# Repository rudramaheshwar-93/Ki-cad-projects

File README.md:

# 🧩 KiCad PCB Projects

A curated collection of PCB designs created using **KiCad**, focused on digital and analog circuit implementations for learning and practical applications.

---

## 📁 Projects

### 🔔 Buzzer PCB

* Simple buzzer driver circuit
* Designed for controlled switching
* 2-layer PCB
  👉 *Includes schematic, PCB layout, and Gerber files*

---

### 🔌 Voltage Regulator PCB (5V → 3.3V)

* LDO-based voltage regulation
* Suitable for ESP32, STM32, and IoT applications
* Stable and compact design
* 2-layer PCB
  👉 *Optimized for clean power delivery*

---

### ➕ Full Adder PCB

* Digital logic implementation of a full adder
* Uses XOR, AND, OR gates
* Demonstrates combinational logic design
* 2-layer PCB
  👉 *Ideal for understanding basic digital circuits*

---

## 🛠️ Tools Used

* KiCad 7.0

---

## 📦 Features

* Clean and readable schematics
* Well-routed PCB layouts
* Manufacturing-ready Gerber files
* Beginner-friendly designs

---

## 🏭 Manufacturing

All projects include **Gerber files** that can be directly uploaded to:

* JLCPCB
* PCBWay

---

## 👤 Author

**Chappidi Rudra Maheshwar Reddy**

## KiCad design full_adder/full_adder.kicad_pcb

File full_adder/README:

# ➕ Full Adder PCB Design

## 📌 Overview

This project implements a **Full Adder circuit** using discrete digital logic gates on a custom-designed PCB.

A full adder performs binary addition of three inputs:

* A
* B
* Carry-in (Cin)

It produces:

* Sum
* Carry-out (Cout)

---

## ⚡ Key Specifications

* Logic Gates Used: XOR, AND, OR
* Function: Binary addition (combinational logic)
* Layers: 2-layer PCB
* Designed using: KiCad

---

## 🔧 Working Principle

* **Sum = A ⊕ B ⊕ Cin**
* **Carry = (A·B) + (Cin·(A ⊕ B))**

This design demonstrates fundamental digital logic implementation on hardware.

---

## 📂 Files Included

* `full_adder.kicad_sch` — Schematic file
* `full_adder.kicad_pcb` — PCB layout file
* `/gerber` — Manufacturing-ready files

---

## 🛠️ Tools Used

* KiCad 7.0

---

## 🏭 Manufacturing

The Gerber files are ready for fabrication using:

* JLCPCB
* PCBWay

---

## 📚 Learning Outcomes

* Understanding combinational logic circuits
* PCB design workflow using KiCad
* Practical implementation of digital electronics

---

## 👤 Author

**Chappidi Rudra Maheshwar Reddy**

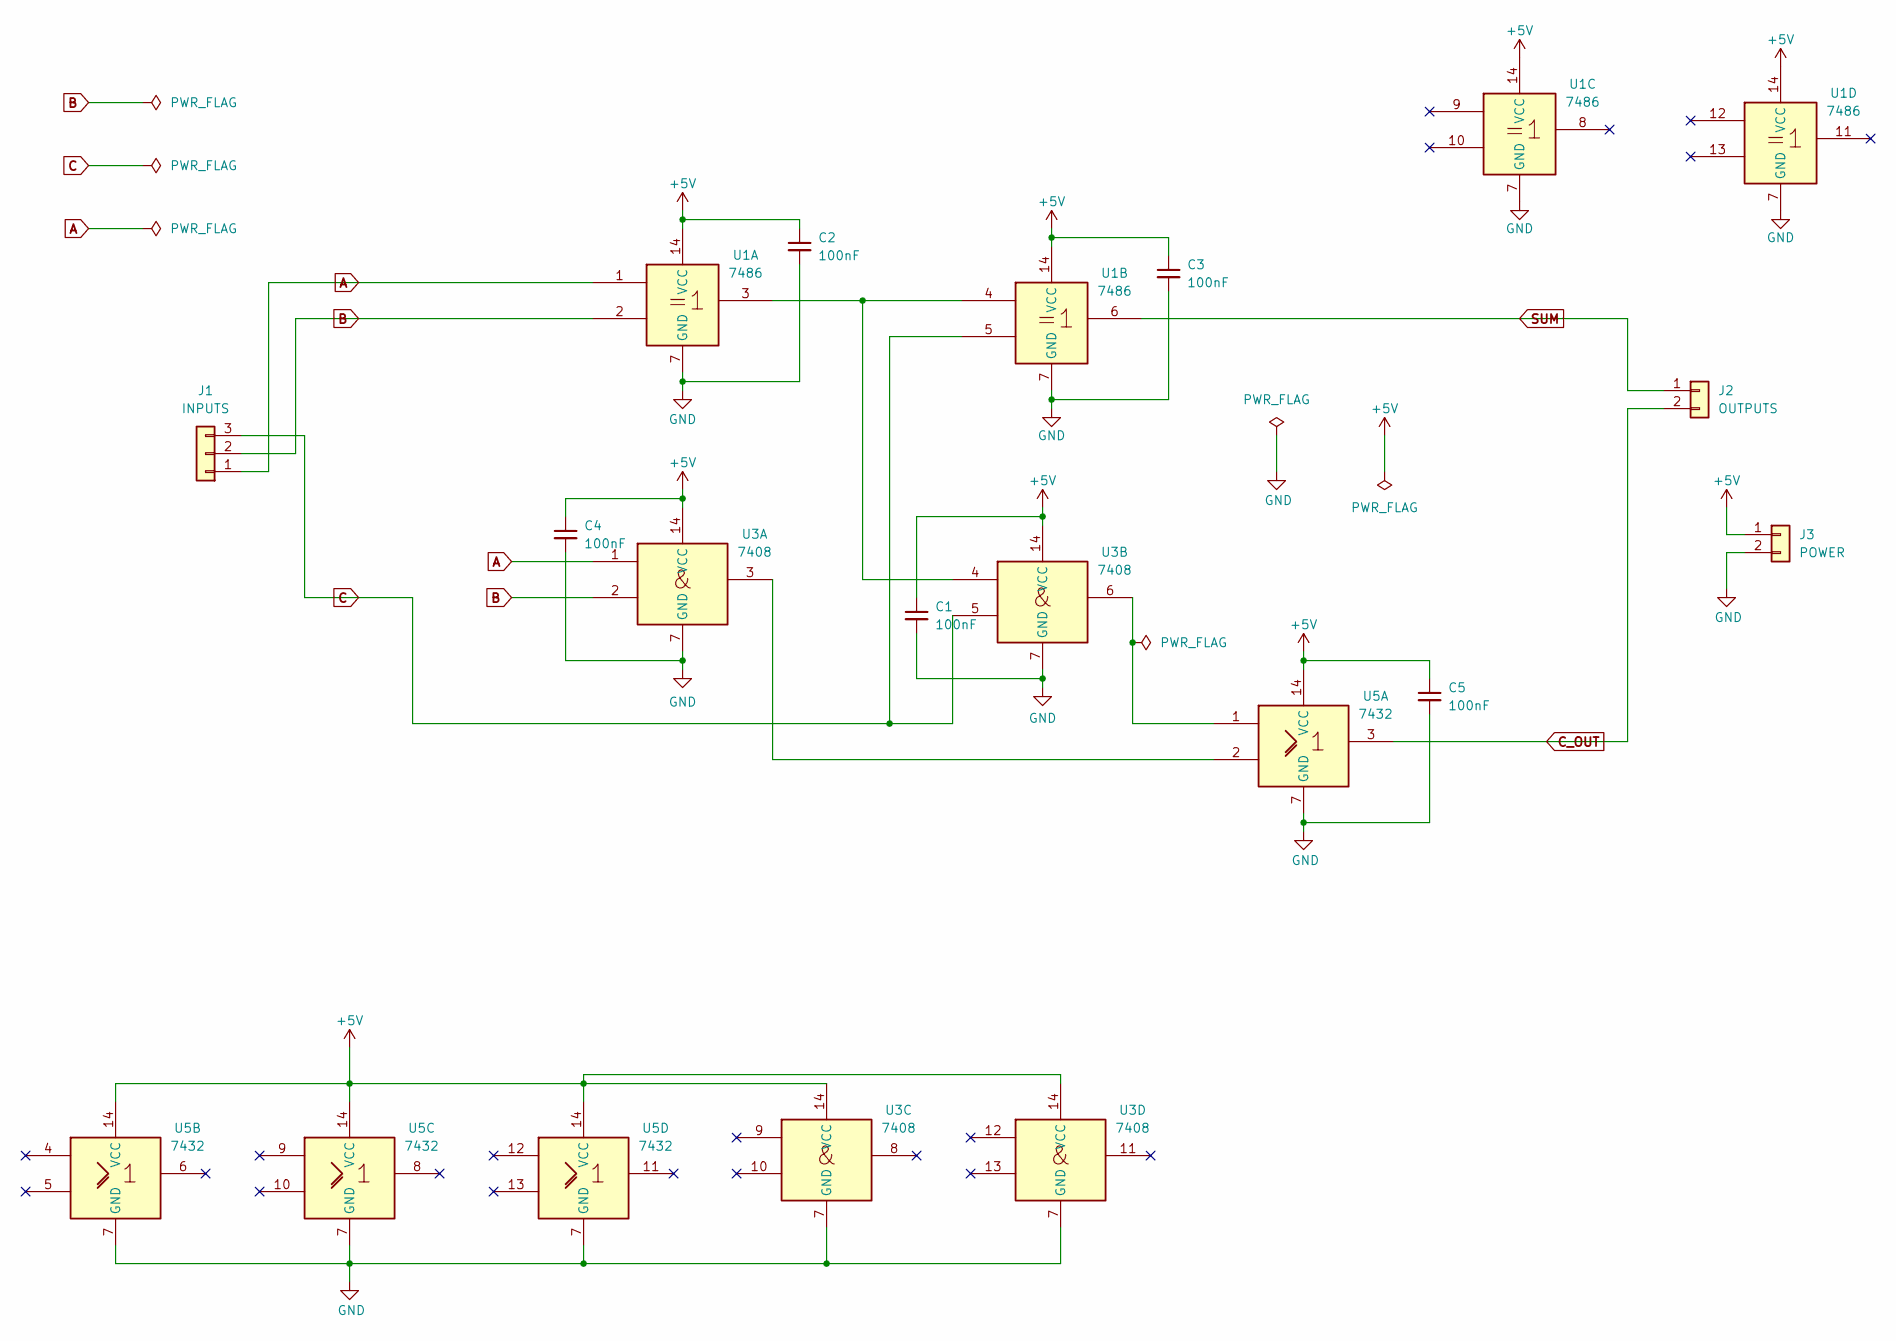
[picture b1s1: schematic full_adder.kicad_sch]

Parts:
C1, C2, C3, C4, C5: 100nF; C_Disc_D5.0mm_W2.5mm_P2.50mm
J1: INPUTS; PinHeader_1x03_P2.54mm_Vertical
J2: OUTPUTS; PinHeader_1x02_P2.54mm_Vertical
J3: POWER; PinHeader_1x02_P2.54mm_Vertical
U1: 7486; DIP-14_W7.62mm
U3: 7408; DIP-14_W7.62mm
U5: 7432; DIP-14_W7.62mm

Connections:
+5V: C1.1, C2.1, C3.1, C4.1, C5.1, J3.1, U1.14 (VCC), U3.14 (VCC), U5.14 (VCC)
A: J1.1, U1.1, U3.1
B: J1.2, U1.2, U3.2
C: J1.3, U1.5, U3.5
C_OUT: J2.2, U5.3
GND: C1.2, C2.2, C3.2, C4.2, C5.2, J3.2, U1.7 (GND), U3.7 (GND), U5.7 (GND)
unnamed: U1.3, U1.4, U3.4
unnamed: U3.3, U5.2
unnamed: U3.6, U5.1
SUM: J2.1, U1.6

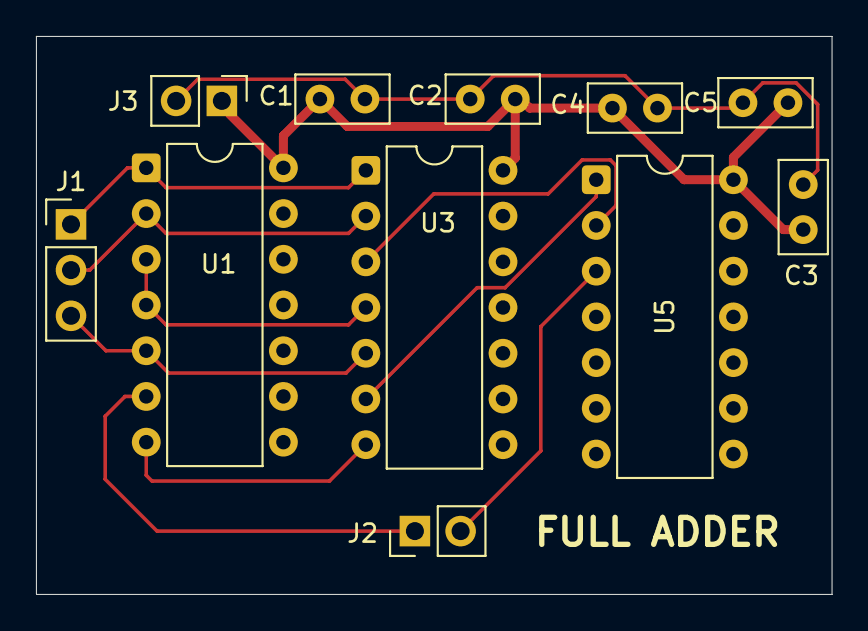
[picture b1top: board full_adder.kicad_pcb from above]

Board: 2 copper layers, 44.2 x 31.0 mm, 11 parts (0 on the bottom side), 10 nets.

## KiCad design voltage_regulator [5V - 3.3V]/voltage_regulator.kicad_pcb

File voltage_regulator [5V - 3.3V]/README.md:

# Voltage Regulator PCB (5V to 3.3V)

## 📌 Overview
A compact 2-layer PCB designed to regulate a 5V input supply down to a
stable 3.3V output using an LDO (Low Dropout) voltage regulator.
Designed for use in embedded systems and IoT applications where 3.3V
logic level components like ESP32, STM32, and nRF24L01 require a clean,
stable power supply.

## ⚡ Key Specifications
- Input Voltage: 5V (USB or external supply)
- Output Voltage: 3.3V regulated
- Regulator Type: LDO (Low Dropout)
- Maximum Output Current: 800mA
- Layers: 2-layer PCB
- PCB Size: compact form factor
- Designed using: KiCad 7.0

## 🖼️ PCB Preview
<!-- Add your 3D render screenshot here -->

## 📂 Repository Structure
​```
voltage-regulator-pcb/
├── voltage_regulator.kicad_pcb   → PCB layout file
├── voltage_regulator.kicad_sch   → Schematic file
├── voltage_regulator.kicad_pro   → Project file
├── gerber/                       → Manufacturing files
│   ├── voltage_regulator-F_Cu.gbr
│   ├── voltage_regulator-B_Cu.gbr
│   ├── voltage_regulator-Edge_Cuts.gbr
│   └── voltage_regulator-job.gbrjob
└── README.md
​```

## 🔧 Components Used
| Component | Value | Purpose |
|---|---|---|
| U1 | AMS1117-3.3 / LM1117 | LDO Voltage Regulator |
| C1 | 10µF Electrolytic | Input Decoupling Capacitor |
| C2 | 10µF Electrolytic | Output Decoupling Capacitor |
| C3 | 100nF Ceramic | High Frequency Bypass |
| LED1 | Green LED | Power Indicator |
| R1 | 1kΩ | LED Current Limiting Resistor |
| J1 | 2-pin Connector | Input (5V) |
| J2 | 2-pin Connector | Output (3.3V) |

## 🔌 How It Works
1. 5V input is fed through J1 connector
2. Input decoupling capacitor C1 filters supply noise
3. LDO regulator drops voltage from 5V to stable 3.3V
4. Output capacitor C2 ensures stability and reduces ripple
5. Green LED indicates the board is powered and outputting correctly
6. Clean 3.3V output is available at J2 connector

## 📐 Design Decisions
- Used AMS1117-3.3 LDO for its wide availability and low dropout voltage
- Added both electrolytic and ceramic capacitors for broadband noise filtering
- Power indicator LED helps verify output during testing without a multimeter
- Wide power traces (0.5mm+) to handle up to 800mA current safely

## 🏭 Manufacturing
Gerber files in `/gerber` folder are tested and verified with zero
DRC errors. Ready to order directly from:
- JLCPCB — jlcpcb.com
- PCBWay — pcbway.com

## 🛠️ Tools Used
- KiCad 7.0 — PCB design and schematic capture
- LTspice — Pre-layout voltage regulation simulation

## 👤 Author
Chappidi Rudra Maheshwar Reddy
GitHub: github.com/rudramaheshwar-93

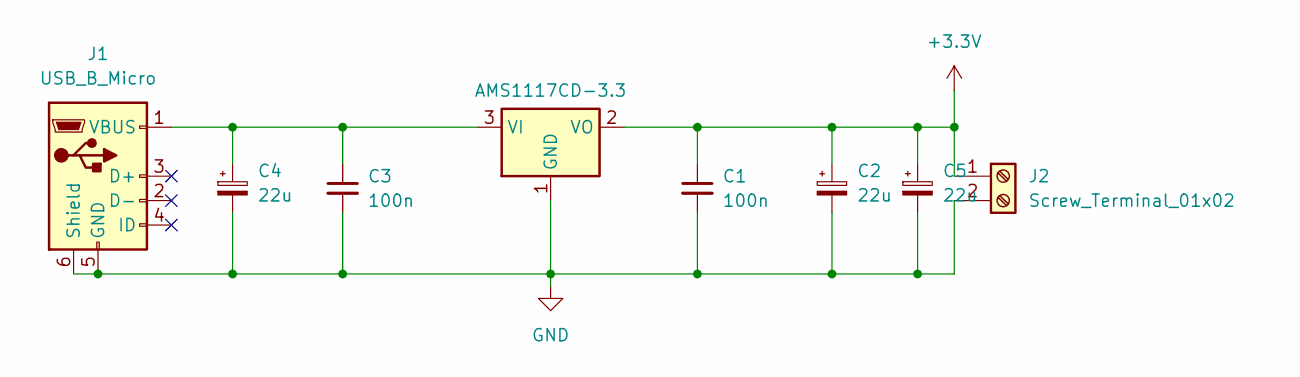
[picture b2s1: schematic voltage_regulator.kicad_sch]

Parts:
C1, C3: 100n; C_01005_0402Metric
C2, C4, C5: 22u; CP_Elec_6.3x7.7
J1: USB_B_Micro; USB_Micro-B_Molex_47346-0001
J2: Screw_Terminal_01x02; TerminalBlock_Phoenix_MKDS-3-2-5.08_1x02_P5.08mm_Horizontal
U1: AMS1117CD-3.3; TO-252-3_TabPin2

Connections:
+3.3V: C1.1, C2.1, C5.1, J2.1, U1.2 (VO)
GND: C1.2, C2.2, C3.2, C4.2, C5.2, J1.5 (GND), J1.6 (Shield), J2.2, U1.1 (GND)
unnamed: C3.1, C4.1, J1.1 (VBUS), U1.3 (VI)

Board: 2 copper layers, 8 parts (0 on the bottom side), 3 nets, no tracks yet.

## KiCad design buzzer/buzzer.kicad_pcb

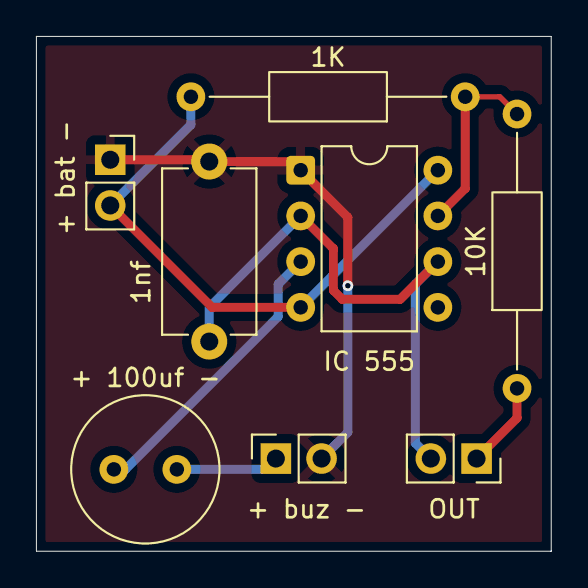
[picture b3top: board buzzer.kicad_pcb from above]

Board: 2 copper layers, 28.6 x 28.6 mm, 8 parts (0 on the bottom side), 7 nets.

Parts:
C1: 1nf; C_Disc_D9.0mm_W5.0mm_P10.00mm
C_polar1: + 100uf -; C_Radial_D8.0mm_H11.5mm_P3.50mm
IC 555: NE555P; DIP-8_W7.62mm
R1: 1K; R_Axial_DIN0207_L6.3mm_D2.5mm_P15.24mm_Horizontal
R2: 10K; R_Axial_DIN0207_L6.3mm_D2.5mm_P15.24mm_Horizontal
TP1: + bat -; PinSocket_1x02_P2.54mm_Vertical
TP2: OUT; PinSocket_1x02_P2.54mm_Vertical
TP3: + buz -; PinSocket_1x02_P2.54mm_Vertical

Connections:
/DIS: IC 555.7 (DISCH), R1.1, R2.2
/TRIG: C1.1, IC 555.2 (TRIG), IC 555.6 (THRES), TP2.2
/out: C_polar1.1, IC 555.3 (OUT)
GND: C1.2, IC 555.1 (GND), TP1.1, TP3.2
unnamed: C_polar1.2, TP3.1
unnamed: R2.1, TP2.1
VCC: IC 555.4 (~RST), IC 555.8 (VCC), R1.2, TP1.2

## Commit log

2026-03-11 first pcb design
2026-03-11 first change
2026-03-11 adding another one
2026-03-11 retry1
2026-03-11 push volt
2026-04-08 Added Full_adder
